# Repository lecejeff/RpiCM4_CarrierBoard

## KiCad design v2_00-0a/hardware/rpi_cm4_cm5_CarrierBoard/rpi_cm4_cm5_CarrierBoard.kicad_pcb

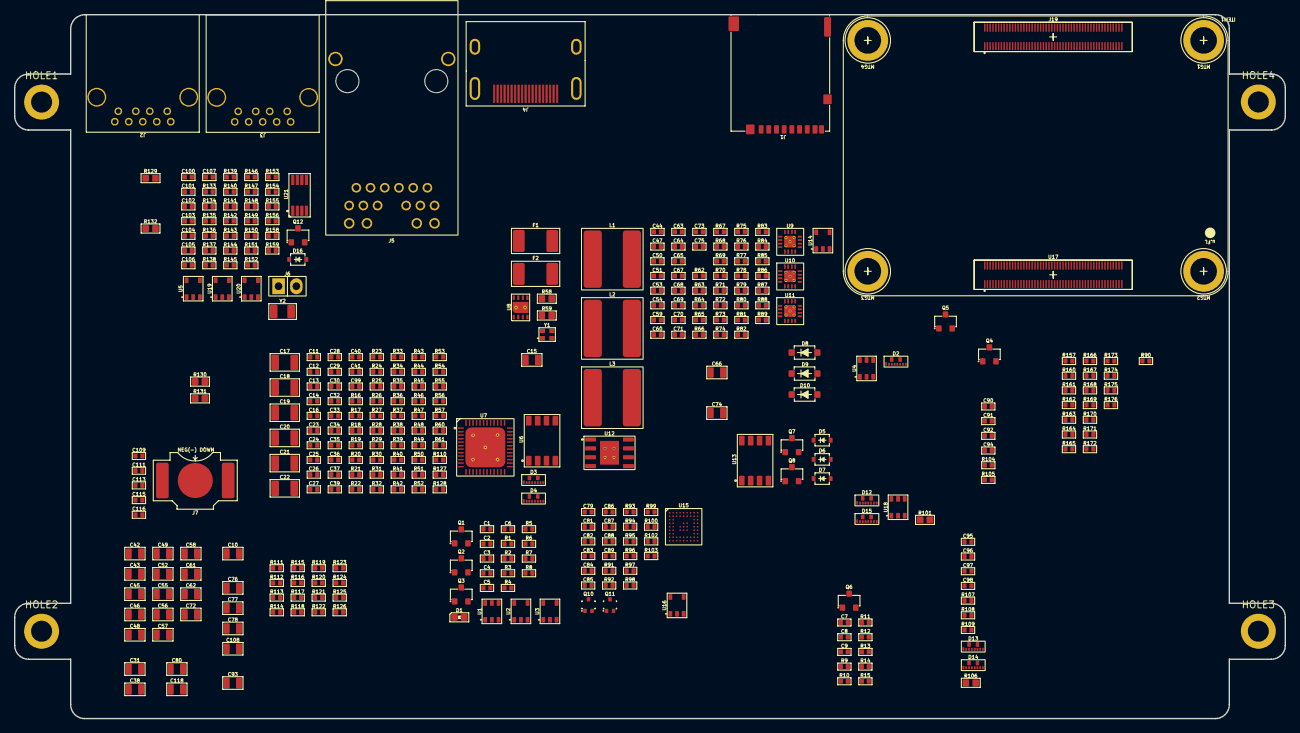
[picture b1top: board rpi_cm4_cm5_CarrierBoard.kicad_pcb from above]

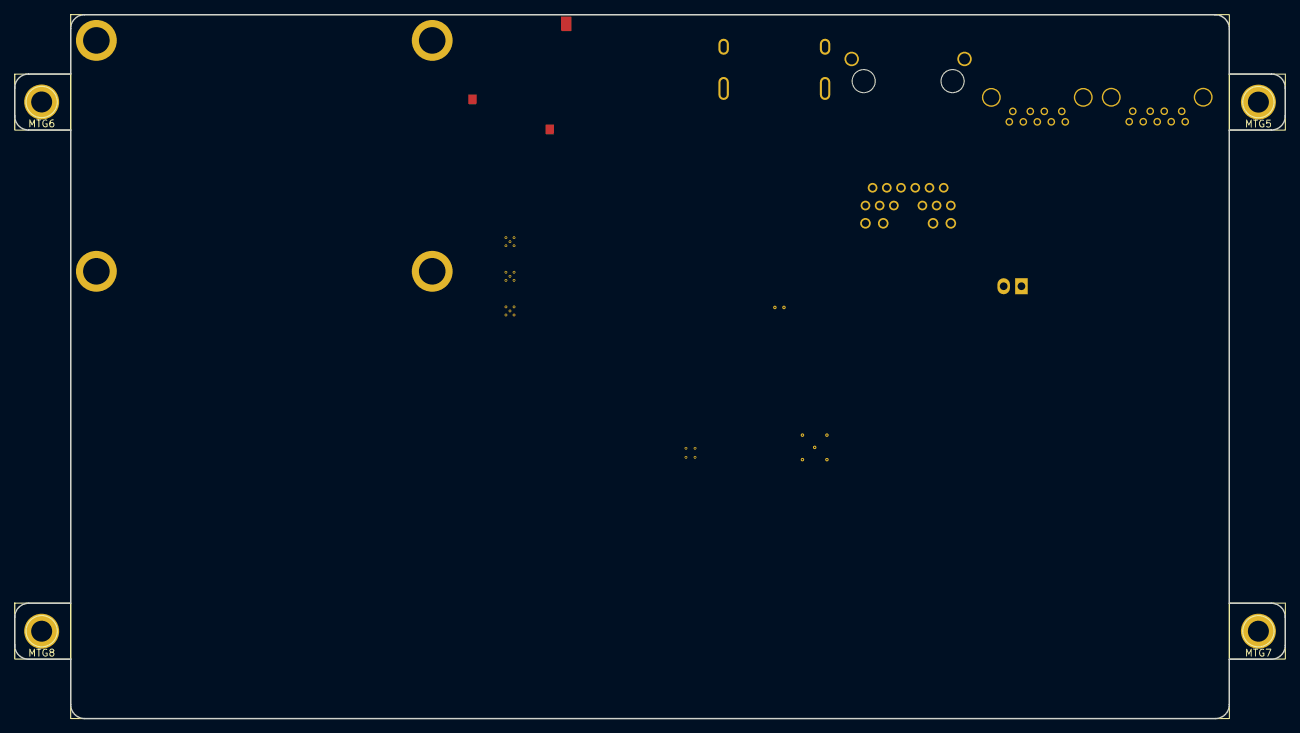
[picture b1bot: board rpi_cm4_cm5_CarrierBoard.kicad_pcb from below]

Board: 2 copper layers, 181.6 x 100.6 mm, 366 parts (5 on the bottom side), 211 nets, no tracks yet.

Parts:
C1, C2, C3, C4, C44, C51, C71, C89: 1n; CAP_NONPOL_0402
C5, C6, C7, C8, C9, C11, C12, C13, C14, C16, C23, C26, C27, C28, C29, C30, C32, C33, C34, C35, C36, C37, C39, C40, C41, C47, C50, C53, C54, C59, C60, C63, C65, C67, C73, C75, C79, C81, C82, C83, C84, C85, C86, C87, C88, C90, C91, C92, C94, C95, C96, C97, C98, C99, C100, C101, C102, C103, C106, C107, C109, C111, C113, C115, C116: 0.1u; CAP_NONPOL_0402
C10, C31, C38, C42, C43, C45, C46, C48, C49, C52, C55, C56, C57, C58, C61, C62, C72, C76, C77, C78, C80, C93, C108, C118: 22u; CAP_NONPOL_0805
C15, C74: 1u; CAP_NONPOL_0805
C17, C18, C19, C20, C21, C22: 47u; CAP_NONPOL_1206
C24, C25: 13p; CAP_NONPOL_0402
C64, C68, C69, C70: 10n; CAP_NONPOL_0402
C66: 10u; CAP_NONPOL_0805
C104, C105: 10p; CAP_NONPOL_0402
D1: LTST-C190KGKT; LED_0603
D2, D3, D4, D12, D13, D14, D15: ESD7016MUTAG; UDFN8
D5, D6, D7, D16: BAT42WS-TP; SOD-323
D8: MMSZ5231B; SOD-123
D9: MMSZ5226B; SOD-123
D10: DDZ9678-7; SOD-123
F1, F2: MINISMDC050F-2; PTC_1812
HOLE1, HOLE2, HOLE3, HOLE4: MTG_hole_cir_5mm_pad_3mm_drill
ITEM1: Raspberry PI CM4 and CM5 symbol; rPI_CM4_CM5
ITEM2: RVT70HSLFWCA0
J1: DM3AT-SF-PEJM5
J2, J3: 0484050003
J4: 2086581001
J5: 0826-1X1T-32-F
J6: M20-9990245; HEADER_2P_2_54MM
J7: 2998TR
J19: RPI_CMx_A; DF40HC(3.0)-100DS-0.4V
L1, L2, L3: SRN8040-2R2Y; SRN8040
MTG1, MTG2, MTG3, MTG4: 9774030151R
MTG5, MTG6, MTG7, MTG8: M0504-25-AL-7
Q1, Q2, Q3, Q4, Q5, Q6, Q7, Q8, Q12: 2N7002; SOT-23-3
Q10, Q11: SSM3K56FS,LF; SC-75
R1: 1K; RES_0402
R2, R3, R5, R6, R9, R10, R11, R12, R15, R46, R47, R48, R49, R51, R52, R54, R55, R56, R57, R61, R62, R65, R66, R67, R68, R70, R72, R73, R74, R75, R77, R78, R80, R83, R88, R89, R90, R91, R92, R93, R94, R100, R104, R105, R110, R111, R112, R113, R116, R119, R120, R133, R134, R138, R142, R147: 10K; RES_0402
R4, R14, R53: 1Meg; RES_0402
R7, R107, R108: 470R; RES_0402
R8, R60, R114, R115, R117, R118, R121, R122, R123, R124, R125, R126, R135, R136, R137, R139, R140, R141, R143, R146, R148, R149, R150, R153, R154, R155: 22R; RES_0402
R13, R16, R17, R18, R19, R20, R21, R22, R23, R24, R25, R26, R27, R28, R29, R30, R31, R32, R33, R34, R35, R36, R37, R38, R39, R40, R41, R42, R43, R44, R45, R63, R64, R85, R95, R96, R97, R109, R127, R128, R151, R152, R157, R160, R161, R162, R163, R164, R165, R166, R167, R168, R169, R170, R171, R172, R173, R174, R175, R176: 0R; RES_0402
R50: 1K6; RES_0402
R58, R59, R101, R106, R129, R130, R131, R132: 0R; RES_0603
R69: 3K24; RES_0402
R71: 1K91; RES_0402
R76: 8K06; RES_0402
R79, R81, R82, R158: 30K1; RES_0402
R84, R86, R87: 100K; RES_0402
R98, R99, R102, R103, R144, R145: 4K7; RES_0402
R156, R159: 510K; RES_0402
U1: STM6710DWB6F; SOT-23-6
U2, U3, U5, U16, U19: SN74LVC1G125DBVR; SOT-23-5
U4, U18: AP22913W6-7; SOT-23-6
U6: SST25VF512A; SOIC-8-150mil
U7: UPD720202K8-711-BAA-A; 48-VFQFN-EP
U8: AP2192AFGEG-7; U-DFN3030-8
U9, U10, U11: TLV62130ARGTR; VQFN-16-EP
U12: TPS7A7002DDAR; SO-8-150mil-EP
U13: SE555DR; SOIC-8-150mil
U14: SN74LVC1G14DBVR; SOT-23-5
U15: SN65DSI84ZXHR; NFBGA-64
U17: RPI_CMx_B; DF40HC(3.0)-100DS-0.4V
U20: SN74LVC1G07DBVR; SOT-23-5
U21: MCP7940NT-I/MS; MSOP-8
Y1: 24MHz; 4-SMD_2mmx1_6mm
Y2: 32.768kHz; 2-SMD_3_2mmx1_5mm

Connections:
1V0_CB: C32.2, C33.2, C34.2, C35.2, C36.2, C37.2, C38.2, C39.2, C48.2, C49.2, C53.2, R1.2, R80.2, R81.2, U7.6 (VDD10), U7.9 (VDD10), U7.21 (VDD10), U7.30 (VDD10), U7.33 (VDD10), U7.39 (VDD10), U7.42 (VDD10), U12.6 (OUT)
1V8_CB: C2.2, C51.2, C52.2, C54.2, C72.2, C73.2, C80.2, C81.2, C82.2, C83.2, C84.2, C85.2, C86.2, C87.2, D10.1 (K), L3.2, Q10.1 (G), Q11.1 (G), R75.2, R77.2, R78.2, R95.1, R99.2, R103.2, U1.3 (V3IN), U11.14 (VOS), U12.3 (IN), U15.A9 (VCC), U15.B8 (VCC), U15.D6 (VCC), U15.E5 (VCC), U15.E6 (VCC), U15.F6 (VCC), U15.J2 (VCC)
1V8_CMx: C76.2, C111.2, J19.88 (CM4_1V8_OUT), J19.90 (CM4_1V8_OUT)
3V3_CB: C3.2, C4.2, C5.2, C6.2, C7.2, C15.2, C16.2, C23.2, C26.2, C27.2, C28.2, C29.2, C30.2, C31.2, C42.2, C43.2, C44.2, C45.2, C46.2, C47.2, C50.2, C67.2, C71.2, C78.2, C88.2, C90.2, C99.2, C103.1, C107.1, C108.2, C113.2, C115.2, C116.2, D8.1 (K), D9.1 (K), D16.2 (A), J1.10 (CD_A), J19.77 (+5V), J19.79 (+5V), J19.81 (+5V), J19.83 (+5V), J19.85 (+5V), J19.87 (+5V), L1.2, L2.2, R3.2, R5.2, R6.2, R9.2, R11.2, R12.2, R48.2, R49.2, R51.2, R52.1, R55.1, R56.1, R57.1, R61.1, R67.2, R68.2, R70.2, R72.2, R73.2, R74.2, R98.2, R102.2, R107.1, R108.1, R112.2, R119.2, R120.2, R138.2, R144.2, R145.2, R151.2, R156.2, R159.2, U1.1 (V1IN), U1.2 (V2IN), U2.5 (VCC), U3.5 (VCC), U4.4 (IN), U4.6 (IN), U6.8 (VDD), U7.3 (AVDD33), U7.12 (VDD33), U7.22 (VDD33), U7.25 (AVDD33), U7.34 (VDD33), U7.43 (VDD33), U8.2 (IN), U9.14 (VOS), U10.14 (VOS), U14.5 (VCC), U16.5 (VCC), U18.4 (IN), U18.6 (IN), U20.5 (VCC), U21.8 (VDD)
3V3_CMx: C77.2, C101.2, C102.2, C109.2, J19.84 (CM4_3V3_OUT), J19.86 (CM4_3V3_OUT), R62.1, R152.2, U5.5 (VCC), U14.2 (A), U19.5 (VCC)
12V0_CB: C55.2, C56.2, C57.2, C58.2, C59.2, C60.2, C61.2, C62.2, C63.2, C65.2, R79.2, R84.2, R85.2, R86.2, U9.10 (AVIN), U9.11 (PVIN), U9.12 (PVIN), U10.10 (AVIN), U10.11 (PVIN), U10.12 (PVIN), U11.10 (AVIN), U11.11 (PVIN), U11.12 (PVIN), U13.8 (VDD)
/CM4_CM5_CONN_A/CM4_~CM5_BUILD: R112.1, R113.2, R124.2
/CM4_CM5_CONN_A/CMx_~INT: J19.37 (GPIO7), R119.1
/CM4_CM5_CONN_A/ETH_P3_N: J19.5 (ETH_P3_N), J19.6 (ETH_P1_N)
/CM4_CM5_CONN_A/GPIO6: J19.30 (GPIO6), R143.1
/CM4_CM5_CONN_A/GPIO8: J19.39 (GPIO8), R121.1
/CM4_CM5_CONN_A/GPIO10: J19.44 (GPIO10), R148.1
/CM4_CM5_CONN_A/GPIO11: J19.38 (GPIO11), R146.1
/CM4_CM5_CONN_A/GPIO12: J19.31 (GPIO12), R118.1
/CM4_CM5_CONN_A/GPIO14: J19.55 (GPIO14), R126.1
/CM4_CM5_CONN_A/GPIO16: J19.29 (GPIO16), R117.1
/CM4_CM5_CONN_A/GPIO17: J19.50 (GPIO17), R150.1
/CM4_CM5_CONN_A/GPIO18: J19.49 (GPIO18), R125.1
/CM4_CM5_CONN_A/GPIO19: J19.26 (GPIO19), R141.1
/CM4_CM5_CONN_A/GPIO21: J19.25 (GPIO21), R115.1
/CM4_CM5_CONN_A/GPIO23: J19.47 (GPIO23), R124.1
/CM4_CM5_CONN_A/GPIO24: J19.45 (GPIO24), R123.1
/CM4_CM5_CONN_A/GPIO25: J19.41 (GPIO25), R122.1
/CM4_CM5_CONN_A/GPIO26: J19.24 (GPIO26), R140.1
/CM4_CM5_CONN_A/GPIO27: J19.48 (GPIO27), R149.1
/CM4_CM5_CONN_A/GPIO_VREF: J19.78 (GPIO_VREF), R151.1, R152.1
/CM4_CM5_CONN_A/I2C3.I2C_SCL: J19.34 (GPIO5), R144.1, U21.6 (SCL)
/CM4_CM5_CONN_A/I2C3.I2C_SDA: J19.54 (GPIO4), R145.1, U21.5 (SDA)
/CM4_CM5_CONN_A/I2S_DIN: J19.27 (GPIO20), R116.2
/CM4_CM5_CONN_A/RTCC: J19.46 (GPIO22), R111.2
/CM4_CM5_CONN_A/RXD0: J19.51 (GPIO15), R138.1
/CM4_CM5_CONN_A/SPI2.SPI_MISO: J19.40 (GPIO9), R147.2
/CM4_CM5_CONN_A/SPI2.SPI_~CS: R120.1, R121.2
/CM4_CM5_CONN_A/WDOG_IN: J19.28 (GPIO13), R142.2
/CM4_CM5_CONN_B/PCIe_CLK_N: R163.1, R172.1, U17.12 (PCIe_CLK_N)
/CM4_CM5_CONN_B/PCIe_CLK_P: R162.1, R171.1, U17.10 (PCIe_CLK_P)
/CM4_CM5_CONN_B/PCIe_CLK_~REQ: R160.1, R169.1, U17.2 (~PCIe_CLK_REQ)
/CM4_CM5_CONN_B/PCIe_RX_N: R165.1, R174.1, U17.18 (PCIe_RX_N)
/CM4_CM5_CONN_B/PCIe_RX_P: R164.1, R173.1, U17.16 (PCIe_RX_P)
/CM4_CM5_CONN_B/PCIe_TX_N: R167.1, R176.1, U17.24 (PCIe_TX_N)
/CM4_CM5_CONN_B/PCIe_TX_P: R166.1, R175.1, U17.22 (PCIe_TX_P)
/CM4_CM5_CONN_B/PCIe_~RST: R157.1, R168.1, U17.9 (~PCIe_RST)
/CM4_CM5_CONN_B/PCIe_~WAKE: R161.1, R170.1, U17.4 (RSVD/~PCIe_DET_WAKE)
/DSI - LVDS bridge/I2C3.I2C_SCL: Q11.3 (D), R98.1
/DSI - LVDS bridge/I2C3.I2C_SDA: Q10.3 (D), R102.1
/DSI - LVDS bridge/SN65DSI_EN: C89.2, R91.1, R92.2, U15.B1 (EN)
/DSI - LVDS bridge/SYS_~RST: R100.2, U16.2 (A)
/Ethernet/ETH_P0_N: D13.2 (I/O2), J5.10 (TRD1-)
/Ethernet/ETH_P0_P: D13.1 (I/O1), J5.11 (TRD1+)
/Ethernet/ETH_P1_N: D13.5 (I/O4), J5.5 (TRD2-)
/Ethernet/ETH_P1_P: D13.4 (I/O3), J5.4 (TRD2+)
/Ethernet/ETH_P2_N: D13.8 (I/O6), J5.2 (TRD3-)
/Ethernet/ETH_P2_P: D13.7 (I/O5), J5.3 (TRD3+)
/Ethernet/ETH_P3_N: D14.2 (I/O2), J5.9 (TRD4-)
/Ethernet/ETH_P3_P: D14.1 (I/O1), J5.8 (TRD4+)
/Ethernet/ETH_~LED1: D14.7 (I/O5), R109.1
/Ethernet/ETH_~LED2: D14.4 (I/O3), J5.13 (LED_Y_K)
/Ethernet/ETH_~LED3: D14.5 (I/O4), J5.15 (LED_GK_OA)
/HDMI/5V_HDMI0: C91.2, C92.2, C93.2, C94.2, D12.3 (VBUS), D15.3 (VBUS), J4.18 (5V), R105.2, U18.1 (OUT)
/HDMI/HDMI0.CEC: D12.7 (I/O5), J4.13 (CEC)
/HDMI/HDMI0.CLK_N: D12.2 (I/O2), J4.12 (CK-)
/HDMI/HDMI0.CLK_P: D12.1 (I/O1), J4.10 (CK+)
/HDMI/HDMI0.D0_N: D15.8 (I/O6), J4.9 (D0-)
/HDMI/HDMI0.D0_P: D15.7 (I/O5), J4.7 (D0+)
/HDMI/HDMI0.D1_N: D15.5 (I/O4), J4.6 (D1-)
/HDMI/HDMI0.D1_P: D15.4 (I/O3), J4.4 (D1+)
/HDMI/HDMI0.D2_N: D15.2 (I/O2), J4.3 (D2-)
/HDMI/HDMI0.D2_P: D15.1 (I/O1), J4.1 (D2+)
/HDMI/HDMI0.HPD: D12.8 (I/O6), J4.19 (HPD)
/HDMI/HDMI0.SCL: D12.4 (I/O3), J4.15 (SCL)
/HDMI/HDMI0.SDA: D12.5 (I/O4), J4.16 (SDA)
/HDMI/SYS_~RST: R104.2, U18.3 (EN)
/Power Supply/POWER_KILL: R88.1, R89.2
/RESET_SUPERVISOR/EXT_~RST: Q2.1 (G), R4.1
/RESET_SUPERVISOR/PWG: Q1.3 (D), Q3.1 (G), R3.1, R5.1, U1.6 (~RESET), U2.2 (A)
/SD_CARD/SDIO_CLK: D2.5 (I/O4), J1.5 (CLK)
/SD_CARD/SDIO_CMD: D2.4 (I/O3), J1.3 (CMD)
/SD_CARD/SDIO_D0: D2.7 (I/O5), J1.7 (DAT0)
/SD_CARD/SDIO_D1: D2.8 (I/O6), J1.8 (DAT1)
/SD_CARD/SDIO_D2: D2.1 (I/O1), J1.1 (DAT2)
/SD_CARD/SDIO_D3: D2.2 (I/O2), J1.2 (CD/DAT3)
/SD_CARD/SD_CARD_DETECT: J1.9 (CD_B), Q5.1 (G), R10.2
/SD_CARD/SD_PWR_ON: Q4.1 (G), R9.1
/SD_CARD/SD_VDD: C9.2, C10.2, D2.3 (VBUS), J1.4 (VDD), R15.2, U4.1 (OUT)
/USB_3/CM5_USB3_VBUS_EN: R44.1, R45.1, R90.2
/USB_3/PETX_N: C41.2, U7.5 (PETX_N)
/USB_3/PETX_P: C40.2, U7.4 (PETX_P)
/USB_3/U2D1_N: R22.1, U7.36 (U2D1_N)
/USB_3/U2D1_P: R21.1, U7.35 (U2D1_P)
/USB_3/U2D2_N: R30.1, U7.45 (U2D2_N)
/USB_3/U2D2_P: R29.1, U7.44 (U2D2_P)
/USB_3/U3RX1_N: R24.1, U7.32 (U3RXD1_N)
/USB_3/U3RX1_P: R23.1, U7.31 (U3RXD1_P)
/USB_3/U3RX2_N: R31.1, U7.41 (U3RXD2_N)
/USB_3/U3RX2_P: R18.1, U7.40 (U3RXD2_P)
/USB_3/U3TX1_N: C13.1, U7.29 (U3TXD1_N)
/USB_3/U3TX1_P: C11.1, U7.28 (U3TXD1_P)
/USB_3/U3TX2_N: C14.1, U7.38 (U3XTD2_N)
/USB_3/U3TX2_P: C12.1, U7.37 (U3TXD2_P)
/USB_3/USB3_0.U3RXD_N: D3.4 (I/O3), J2.5 (SSRX-), R24.2, R38.2
/USB_3/USB3_0.U3RXD_P: D3.5 (I/O4), J2.6 (SSRX+), R23.2, R39.2
/USB_3/USB3_0.U3TXD_N: D3.7 (I/O5), J2.8 (SSTX-), R20.2, R42.2
/USB_3/USB3_0.U3TXD_P: D3.8 (I/O6), J2.9 (SSTX+), R19.2, R43.2
/USB_3/USB3_0.USB_N: D3.1 (I/O1), J2.2 (D-), R22.2, R40.2
/USB_3/USB3_0.USB_P: D3.2 (I/O2), J2.3 (D+), R21.2, R41.2
/USB_3/USB3_0.USB_VBUS: C17.2, C19.2, C21.2, D3.3 (VBUS), F1.2, J2.1 (VBUS)
/USB_3/USB3_1.U3RXD_N: D4.4 (I/O3), J3.5 (SSRX-), R31.2, R32.2
/USB_3/USB3_1.U3RXD_P: D4.5 (I/O4), J3.6 (SSRX+), R18.2, R33.2
/USB_3/USB3_1.U3TXD_N: D4.7 (I/O5), J3.8 (SSTX-), R17.2, R36.2
/USB_3/USB3_1.U3TXD_P: D4.8 (I/O6), J3.9 (SSTX+), R16.2, R37.2
/USB_3/USB3_1.USB_N: D4.1 (I/O1), J3.2 (D-), R30.2, R34.2
/USB_3/USB3_1.USB_P: D4.2 (I/O2), J3.3 (D+), R29.2, R35.2
/USB_3/USB3_1.USB_VBUS: C18.2, C20.2, C22.2, D4.3 (VBUS), F2.2, J3.1 (VBUS)
/USB_3/USB_HUB.~WAKE: R61.2, U7.48 (~PEWAKE)
/USB_3/USB_HUB_~RST: R110.1, U7.11 (~PONRST)
CGND: J2.10 (CGND), J2.11 (CGND), J3.10 (CGND), J3.11 (CGND), J4.2 (D2S), J4.5 (D1S), J4.8 (D0S), J4.11 (CKS), J4.20 (MT1), J4.21 (MT2), J4.22 (MT3), J4.23 (MT4), J5.17, J5.18, R58.1, R59.1, R101.1, R106.2
GND: C1.1, C2.1, C3.1, C4.1, C5.1, C6.1, C7.1, C8.1, C9.1, C10.1, C15.1, C16.1, C17.1, C18.1, C19.1, C20.1, C21.1, C22.1, C23.1, C24.1, C25.1, C26.1, C27.1, C28.1, C29.1, C30.1, C31.1, C32.1, C33.1, C34.1, C35.1, C36.1, C37.1, C38.1, C39.1, C42.1, C43.1, C45.1, C46.1, C47.1, C48.1, C49.1, C50.1, C52.1, C53.1, C54.1, C55.1, C56.1, C57.1, C58.1, C59.1, C60.1, C61.1, C62.1, C63.1, C64.1, C65.1, C66.1, C67.1, C68.2, C69.2, C70.2, C72.1, C73.1, C74.1, C75.1, C76.1, C77.1, C78.1, C79.1, C80.1, C81.1, C82.1, C83.1, C84.1, C85.1, C86.1, C87.1, C88.1, C89.1, C90.1, C91.1, C92.1, C93.1, C94.1, C95.1, C96.1, C97.1, C98.1, C99.1, C100.1, C101.1, C102.1, C103.2, C104.2, C105.2, C107.2, C108.1, C109.1, C111.1, C113.1, C115.1, C116.1, C118.1, D1.1 (K), D2.6 (GND), D3.6 (GND), D4.6 (GND), D8.2 (A), D9.2 (A), D10.2 (A), D12.6 (GND), D13.3 (VBUS), D13.6 (GND), D14.3 (VBUS), D14.6 (GND), D15.6 (GND), J1.6 (VSS), J2.4 (GND), J2.7 (GND), J3.4 (GND), J3.7 (GND), J4.17 (GND), J6.2, J7.2, J19.1 (GND), J19.2 (GND), J19.7 (GND), J19.8 (GND), J19.13 (GND), J19.14 (GND), J19.22 (GND), J19.23 (GND), J19.32 (GND), J19.33 (GND), J19.42 (GND), J19.43 (GND), J19.52 (GND), J19.53 (GND), J19.59 (GND), J19.60 (GND), J19.65 (GND), J19.66 (GND), J19.71 (GND), J19.74 (GND), J19.98 (GND), MTG1.1, MTG2.1, MTG3.1, MTG4.1, Q2.2 (S), Q3.2 (S), Q5.2 (S), Q6.2 (S), Q7.2 (S), Q8.2 (S), Q12.2 (S), R2.1, R4.2, R10.1, R14.1, R15.1, R46.1, R47.1, R50.1, R54.2, R58.2, R59.2, R62.2, R64.1, R65.1, R69.2, R71.2, R72.1, R73.1, R76.2, R77.1, R80.1, R82.1, R83.1, R87.1, R89.1, R90.1, R92.1, R93.1, R94.1, R100.1, R101.2, R104.1, R105.1, R106.1, R110.2, R111.1, R113.1, R116.1, R129.2, R130.2, R131.2, R132.2, R133.1, R134.1, R142.1, R147.1, U1.5 (GND), U2.1 (~OE), U2.3 (GND), U3.1 (~OE), U3.3 (GND), U4.2 (GND), U4.5 (GND), U5.1 (~OE), U5.3 (GND), U6.4 (GND), U7.27 (IC(L)), U7.49 (GND), U8.1 (GND), U8.9 (GND), U9.6 (AGND), U9.7 (FSW), U9.8 (DEF), U9.15 (PGND), U9.16 (PGND), U9.17 (GND), U10.6 (AGND), U10.7 (FSW), U10.8 (DEF), U10.15 (PGND), U10.16 (PGND), U10.17 (GND), U11.6 (AGND), U11.7 (FSW), U11.8 (DEF), U11.15 (PGND), U11.16 (PGND), U11.17 (GND), U12.8 (GND), U12.9 (EP), U13.1 (GND), U14.3 (GND), U15.A2 (GND), U15.A8 (GND), U15.B9 (GND), U15.D5 (GND), U15.E4 (GND), U15.F4 (GND), U15.F5 (GND), U15.H9 (GND), U16.1 (~OE), U16.3 (GND), U17.7 (GND), U17.8 (GND), U17.13 (GND), U17.14 (GND), U17.19 (GND), U17.20 (GND), U17.25 (GND), U17.26 (GND), U17.31 (GND), U17.32 (GND), U17.37 (GND), U17.38 (GND), U17.44 (GND), U17.50 (GND), U17.55 (GND), U17.56 (GND), U17.61 (GND), U17.62 (GND), U17.67 (GND), U17.68 (GND), U17.73 (GND), U17.74 (GND), U17.79 (GND), U17.80 (GND), U17.85 (GND), U17.86 (GND), U17.91 (GND), U17.92 (GND), U17.97 (GND), U17.98 (GND), U18.2 (GND), U18.5 (GND), U19.1 (~OE), U19.3 (GND), U20.3 (GND), U21.4 (GND), Y1.2 (GND), Y1.4 (GND)
unnamed: C11.2, R19.1
unnamed: C12.2, R16.1
unnamed: C13.2, R20.1
unnamed: C14.2, R17.1
unnamed: D1.2 (A), R7.2
unnamed: D5.1 (K), D6.1 (K), D7.2 (A), R65.2, U10.13 (EN), U11.13 (EN)
unnamed: D6.2 (A), R63.2, R64.2
unnamed: D7.1 (K), R66.1
unnamed: D16.1 (K), R158.2
unnamed: HOLE1.1, R132.1
unnamed: HOLE2.1, R129.1
unnamed: HOLE3.1, R130.1
unnamed: HOLE4.1, R131.1
unnamed: J5.16 (LED_GA_OK), R108.2, R109.2
unnamed: J5.14 (LED_Y_A), R107.2
unnamed: C95.2, J5.12 (TRCT1)
unnamed: C96.2, J5.6 (TRCT2)
unnamed: C97.2, J5.1 (TRCT3)
unnamed: C98.2, J5.7 (TRCT4)
unnamed: J19.97 (CAM_GPIO/GPIO34), R136.1
unnamed: J19.99 (GLOBAL_EN/PMIC_EN), U20.4 (Y)
unnamed: J19.92 (RUN_PG/PWR_BTN), U5.2 (A)
unnamed: J19.75 (SD_PWR_ON), R137.1
unnamed: J6.1, J19.20 (~EEPROM_WP)
unnamed: J19.100 (~EXTRST/GPIO35), R154.1
unnamed: J19.21 (~PI_LED_ACT), R114.1
unnamed: J19.95 (~PI_LED_PWR), R135.1
unnamed: J19.93 (~RPIBOOT), Q12.3 (D)
unnamed: L1.1, U10.1 (SW), U10.2 (SW), U10.3 (SW)
unnamed: L2.1, U9.1 (SW), U9.2 (SW), U9.3 (SW)
unnamed: L3.1, U11.1 (SW), U11.2 (SW), U11.3 (SW)
unnamed: Q1.2 (S), Q2.3 (D)
unnamed: Q3.3 (D), R6.1, U3.2 (A)
unnamed: Q4.3 (D), Q6.1 (G), R11.1
unnamed: Q4.2 (S), Q5.3 (D)
unnamed: Q6.3 (D), R12.1, R13.1
unnamed: Q7.3 (D), R79.1, U9.13 (EN)
unnamed: Q7.1 (G), U13.3 (OUT)
unnamed: C74.2, Q8.3 (D), R86.1, R87.2, U13.2 (TRIG)
unnamed: C75.2, Q8.1 (G), R88.2
unnamed: Q10.2 (S), R103.1, U15.J1 (SDA)
unnamed: Q11.2 (S), R99.1, U15.H1 (SCL)
unnamed: C100.2, Q12.1 (G), R139.1
unnamed: C1.2, R1.1, R2.2, U1.4 (V4IN)
unnamed: R7.1, U2.4 (Y)
unnamed: R8.1, U3.4 (Y)
unnamed: C8.2, R13.2, R14.2, U4.3 (EN)
unnamed: R153.1, U5.4 (Y)
unnamed: R54.1, U6.6 (SCK), U7.15 (SPISCK)
unnamed: R57.2, U6.5 (SI), U7.16 (SPISI)
unnamed: R56.2, U6.2 (SO), U7.13 (SPISO)
unnamed: R55.2, U6.1 (~CE), U7.14 (~SPICS)
unnamed: R52.2, U6.3 (~WP), U6.7 (~HOLD)
unnamed: R26.1, U7.20 (PPON1)
unnamed: R28.1, U7.18 (PPON2)
unnamed: R50.2, U7.26 (RREF)
unnamed: C24.2, R53.2, U7.24 (XT1), Y1.1 (XI)
unnamed: C25.2, R53.1, U7.23 (XT2), Y1.3 (XO)
unnamed: R25.1, U7.19 (~OCI1)
unnamed: R27.1, U7.17 (~OCI2)
unnamed: R60.2, U7.10 (~PECREQ)
unnamed: R51.1, U7.46 (~SMI)
unnamed: R26.2, R44.2, R46.2, U8.3 (EN1)
unnamed: R28.2, R45.2, R47.2, U8.4 (EN2)
unnamed: R25.2, R48.1, R127.2, U8.8 (FLG1)
unnamed: R27.2, R49.1, R128.2, U8.5 (FLG2)
unnamed: F1.1, U8.7 (OUT1)
unnamed: F2.1, U8.6 (OUT2)
unnamed: C71.1, R70.1, R71.1, U9.5 (FB)
unnamed: R66.2, R67.1, U9.4 (PG)
unnamed: C70.1, U9.9 (SS)
unnamed: C44.1, R68.1, R69.1, U10.5 (FB)
unnamed: R74.1, U10.4 (PG)
unnamed: C68.1, U10.9 (SS)
unnamed: C51.1, R75.1, R76.1, U11.5 (FB)
unnamed: R78.1, R83.2, U11.4 (PG), U12.2 (EN)
unnamed: C69.1, U11.9 (SS)
unnamed: R81.1, R82.2, U12.7 (FB)
unnamed: C64.2, U13.5 (CONT)
unnamed: C66.2, R84.1, U13.6 (THRES), U13.7 (DISCH)
unnamed: R85.1, U13.4 (~RESET)
unnamed: R63.1, U14.4 (Y)
unnamed: R93.2, R95.2, U15.A1 (ADDR)
unnamed: R96.2, U15.J9 (IRQ)
unnamed: R94.2, R97.2, U15.H2 (REFCLK)
unnamed: C79.2, C118.2, U15.J8 (VCORE)
unnamed: R91.2, U16.4 (Y)
unnamed: R154.2, U19.2 (A)
unnamed: R155.1, U19.4 (Y)
unnamed: C106.1, R156.1, U20.2 (A)
unnamed: C106.2, R159.1, U21.7 (MFP)
unnamed: J7.1, R158.1, U21.3 (VBAT)
unnamed: C104.1, U21.1 (X1), Y2.2 (XO)
unnamed: C105.1, U21.2 (X2), Y2.1 (XI)

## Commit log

2023-10-22 Initial commit of design files for RPI-CM4 CarrierBoard
2023-10-22 TEst de commit
2023-10-25 Update sch cartridge Start PCB component placement
2023-11-06 Upload latest schematics, boards and sch.pdf
2023-12-17 Update GIT repo with poduction file BOM Sch pdf Pcb pdf Step model Gerbers (native + archive) Design files (sch + pcb)
2023-12-17 Update silk placement in gerbers, re-export all output files associated
2023-12-17 Remove unversioned pdf file
2023-12-17 Add schematics .pdf
2023-12-17 Update sch.pdf CM4_b part, PCIe_RSTn pin type set to output
2023-12-20 Correct schematic, 3K3 R234 should read 3K24
2023-12-21 Import working gerbers and stencil to git repo
2023-12-21 Update SPI0 to SPI2 net name and net group in schematics, and related output files
2024-01-31 Add FRM to repo Add dsPIC33CK library source code to repo Add CM4 device tree overlays and config.txt to repo
2024-01-31 Add schematic .pdf to repo
2024-02-02 Add PCIe USB bridge memory programming tool and FW image
2024-06-02 Add device tree overlay WIP
2025-11-05 Commit rev 0B to git
2025-12-07 Create RPI CMx CB KiCad project and push initial design to Git
2025-12-11 Add power supply schematic sheet
2025-12-14 Add schematic pages for SOM_CONN_A/B, DSI to LVDS bridge, Ethernet and HDMI
2025-12-22 Update schematics (several new hierarchical pages, updates bus labels)
2025-12-23 Add new page and update schematics
2025-12-24 Add design notes (power table) and latest changes to power supply and power input
2025-12-27 Add TFT schematic pages (power + connector)
2025-12-29 Update schematic
2026-01-01 Add and modify existing schematics
2026-01-01 Remove RPI CMx from RPI CM4 repository
